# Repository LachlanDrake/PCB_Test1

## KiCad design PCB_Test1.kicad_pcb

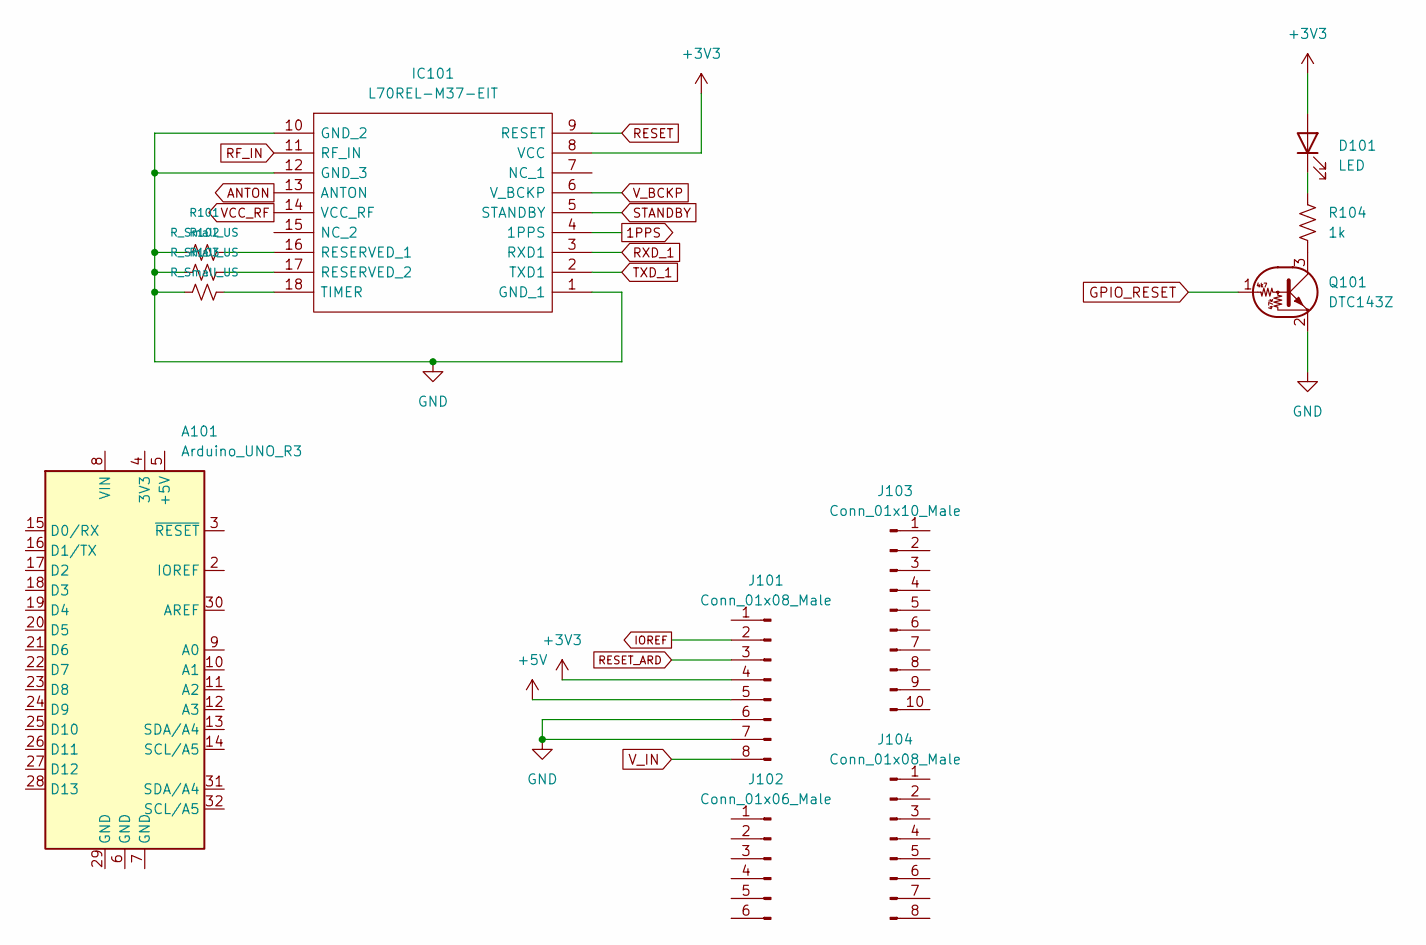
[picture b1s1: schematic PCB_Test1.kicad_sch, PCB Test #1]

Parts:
A101: Arduino_UNO_R3
D101: LED; LED_1210_3225Metric
IC101: L70REL-M37-EIT; L70RELM37EIT; Mouser Part Number 277-L70REL-M37-EIT
J101, J104: Conn_01x08_Male; PinHeader_1x08_P2.54mm_Vertical
J102: Conn_01x06_Male; PinHeader_1x06_P2.54mm_Vertical
J103: Conn_01x10_Male; PinHeader_1x10_P2.54mm_Vertical
Q101: DTC143Z; SOT-416
R101, R102, R103: R_Small_US; R_1206_3216Metric
R104: 1k; R_1206_3216Metric

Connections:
1PPS: IC101.4 (1PPS)
+3V3: D101.2 (A), IC101.8 (VCC), J101.4
+5V: J101.5
ANTON: IC101.13 (ANTON)
GND: IC101.1 (GND_1), IC101.10 (GND_2), IC101.12 (GND_3), J101.6, J101.7, Q101.2 (E), R101.1, R102.1, R103.1
GPIO_RESET: Q101.1 (B)
IOREF: J101.2
unnamed: D101.1 (K), R104.1
unnamed: IC101.16 (RESERVED_1), R101.2
unnamed: IC101.17 (RESERVED_2), R102.2
unnamed: IC101.18 (TIMER), R103.2
unnamed: Q101.3 (C), R104.2
RESET: IC101.9 (RESET)
RESET_ARD: J101.3
RF_IN: IC101.11 (RF_IN)
RXD_1: IC101.3 (RXD1)
STANDBY: IC101.5 (STANDBY)
TXD_1: IC101.2 (TXD1)
VCC_RF: IC101.14 (VCC_RF)
V_BCKP: IC101.6 (V_BCKP)
V_IN: J101.8

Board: 2 copper layers, 12 parts (0 on the bottom side), 7 nets, no tracks yet.

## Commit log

2022-12-21 Add readme file
2022-12-21 Add LED circuit and GNSS module to schematic
2022-12-23 Add L70-R GPS module to schematic
2022-12-24 Add Arduino to schematic
2022-12-24 Assign footprints
2023-01-01 Added male headers for arduino uno r3
2023-01-02 Add nets to all header pins
2023-01-18 minor changes
